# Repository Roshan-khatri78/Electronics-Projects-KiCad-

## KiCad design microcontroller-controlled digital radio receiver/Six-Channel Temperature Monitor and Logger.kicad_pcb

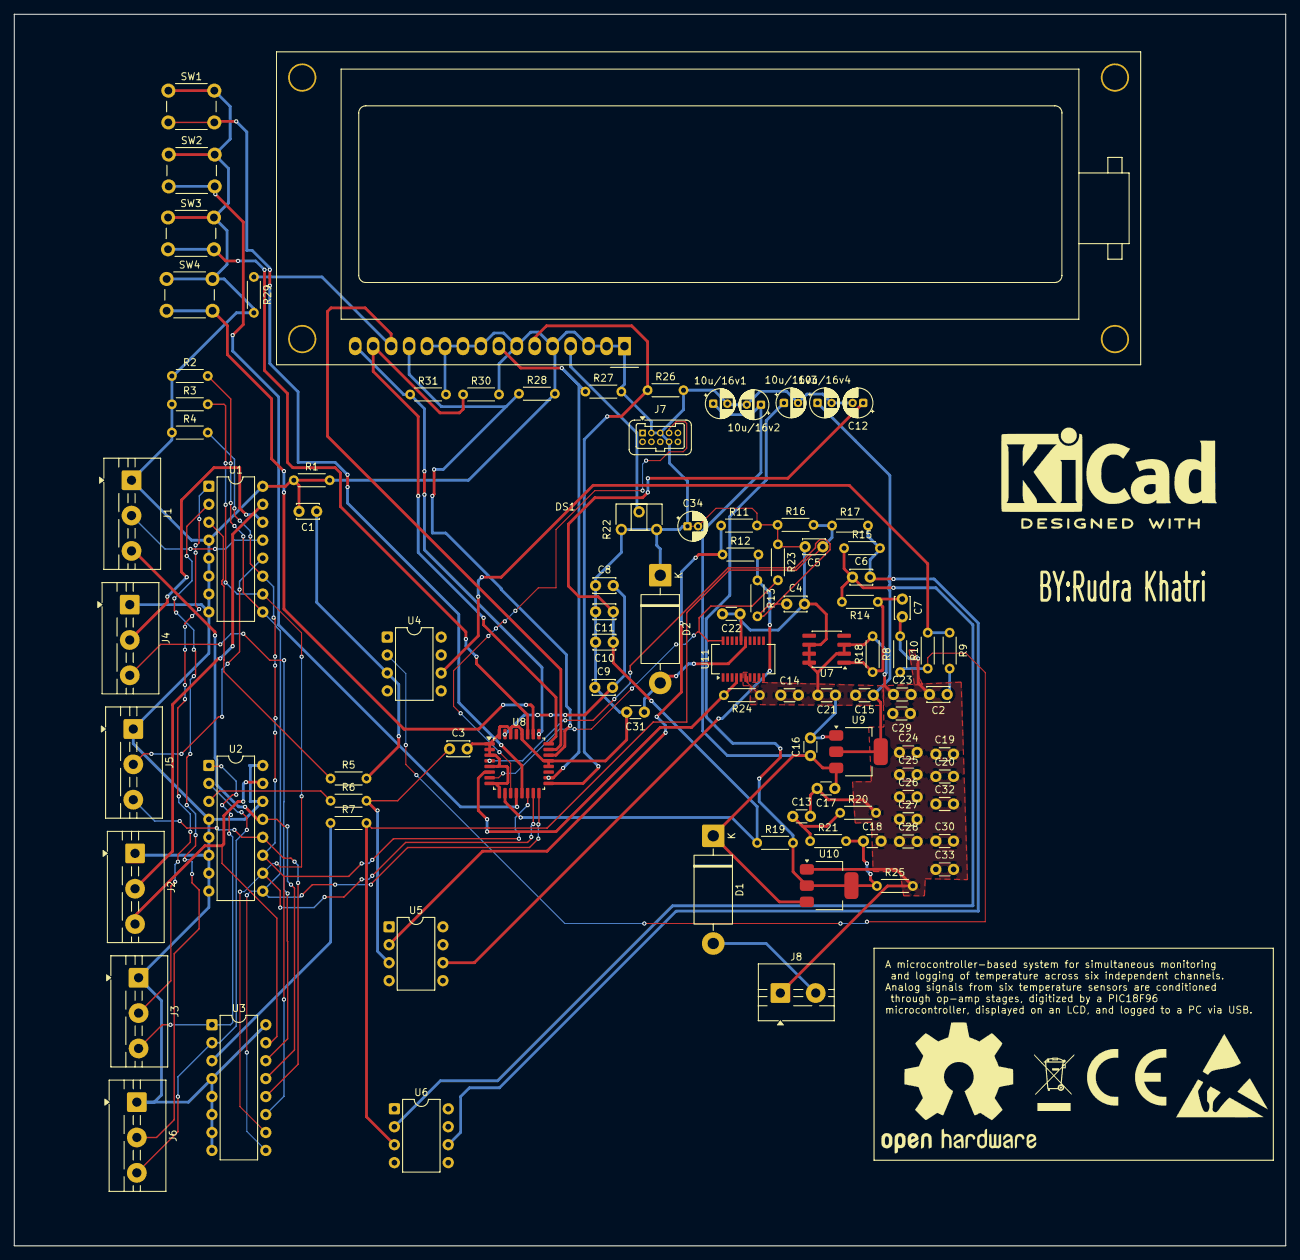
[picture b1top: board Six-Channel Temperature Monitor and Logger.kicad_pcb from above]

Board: 4 copper layers, 179.9 x 174.2 mm, 95 parts (0 on the bottom side), 53 nets.

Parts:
10u/16v1, 10u/16v2, 10u/16v3, 10u/16v4: C_Polarized; CP_Radial_D4.0mm_P2.00mm
C1, C2, C3, C4, C5, C7: C; C_Disc_D3.0mm_W2.0mm_P2.50mm
C6: 1n; C_Disc_D3.0mm_W2.0mm_P2.50mm
C8: 100n; C_Disc_D3.0mm_W2.0mm_P2.50mm
C9, C10, C11: 1; C_Disc_D3.0mm_W2.0mm_P2.50mm
C12: 10v/10u; CP_Radial_D4.0mm_P1.50mm
C13, C14, C15, C16, C17, C18, C31: C; C_Disc_D3.0mm_W1.6mm_P2.50mm
C19, C20, C21, C22, C23, C24, C25, C26, C27, C28, C29, C30, C33: 100n; C_Disc_D3.0mm_W1.6mm_P2.50mm
C32: 1n; C_Disc_D3.0mm_W1.6mm_P2.50mm
C34: 10u/10v; CP_Radial_D4.0mm_P1.50mm
D1, D2: MBR340; D_DO-201AD_P15.24mm_Horizontal
DS1: HY1602E
J1, J2, J3, J4, J5, J6: Screw_Terminal_01x03; TerminalBlock_MaiXu_MX126-5.0-03P_1x03_P5.00mm
J7: Conn_02x05_Odd_Even; Harwin_Gecko-G125-FVX1005L0X_2x05_P1.25mm_Vertical
J8: Screw_Terminal_01x02; TerminalBlock_MaiXu_MX126-5.0-02P_1x02_P5.00mm
R1: 470hm; R_Axial_DIN0204_L3.6mm_D1.6mm_P5.08mm_Horizontal
R2, R3, R4, R14, R15, R16, R17, R23, R24: 10k; R_Axial_DIN0204_L3.6mm_D1.6mm_P5.08mm_Horizontal
R5, R6, R7, R18, R20, R21: 1k; R_Axial_DIN0204_L3.6mm_D1.6mm_P5.08mm_Horizontal
R8, R9, R10, R11, R12, R13, R25, R26, R27, R28, R29, R30, R31: R; R_Axial_DIN0204_L3.6mm_D1.6mm_P5.08mm_Horizontal
R19: 10ohm; R_Axial_DIN0204_L3.6mm_D1.6mm_P5.08mm_Horizontal
R22: Potentiometer; Potentiometer_ACP_CA6-H2,5_Horizontal
SW1, SW2, SW3, SW4: SW_Push; SW_PUSH_6mm_H4.3mm
U1, U2, U3: 4051; DIP-16_W7.62mm
U4, U5, U6: OP07; DIP-8_W7.62mm
U7: TL431D; SOIC-8_3.9x4.9mm_P1.27mm
U8: C8051F350; LQFP-32_7x7mm_P0.8mm
U9, U10: LD1117S12TR_SOT223; SOT-223-3_TabPin2
U11: FT231XS; SSOP-20_3.9x8.7mm_P0.635mm

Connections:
+5V: 10u/16v4.1, C15.1, U9.2 (VO)
+5v: 10u/16v1.2, 10u/16v2.2, 10u/16v3.2, 10u/16v4.2, C1.2, C2.2, C3.2, C4.2, C5.2, C7.2, C8.1, C9.1, C10.2, C11.2, C12.2, C13.2, C14.1, C14.2, C15.2, C16.2, C17.2, C18.2, C19.1, C19.2, C20.1, C20.2, C21.1, C21.2, C22.1, C22.2, C23.1, C23.2, C24.1, C24.2, C25.1, C25.2, C26.1, C26.2, C27.1, C27.2, C28.1, C28.2, C29.1, C29.2, C30.1, C30.2, C31.2, C32.1, C32.2, C33.1, C33.2, C34.1, C34.2, D2.1 (K), DS1.1 (LEDK), DS1.2 (LEDA), DS1.3 (VSS), DS1.5 (Vo), DS1.7 (R/~W), DS1.9 (DB0), DS1.10 (DB1), DS1.11 (DB2), DS1.12 (DB3), J1.1, J2.1, J3.1, J4.1, J5.1, J6.1, J7.2, J7.3, J7.9, J8.1, R1.1, R1.2, R2.1, R3.1, R4.1, R8.2, R11.2, R16.1, R18.2, R20.2, R22.1, R22.3, R23.1, R24.1, R25.2, R26.2, R27.2, R28.2, R29.2, R30.2, R31.2, SW1.1, SW2.1, SW3.1, SW4.1, U1.4 (X7), U1.5 (X5), U1.6 (Inh), U1.7 (VEE), U1.8 (VSS), U1.16 (VDD), U2.4 (X7), U2.5 (X5), U2.6 (Inh), U2.7 (VEE), U2.8 (VSS), U2.14 (X1), U2.16 (VDD), U3.4 (X7), U3.5 (X5), U3.6 (Inh), U3.7 (VEE), U3.8 (VSS), U3.16 (VDD), U7.2 (A), U7.3 (A), U7.6 (A), U7.7 (A), U7.8 (REF), U8.1 (AIN0.2), U8.2 (AIN0.1), U8.3 (GND), U8.5 (AIN0.4), U8.8 (AIN0.7), U8.9 (AGND), U8.20 (DGND), U8.21 (VDD), U8.28 (AIN0.6), U8.30 (AIN0.0), U8.32 (VREF-), U9.1 (GND), U10.1 (GND), U11.6 (GND), U11.16 (GND)
/3v3: 10u/16v3.1, C18.1, R19.2, R21.2, R25.1, U10.2 (VO)
/RXD: R24.2, U8.6 (TX/P0.4), U11.4 (RXD)
/TXD: R23.2, U8.7 (RX/P0.5), U11.20 (TXD)
/a03: C4.1, R13.2, U8.4 (AIN0.3)
/a05: C2.1, R9.2
/ic6: C1.1, R5.2, U4.3 (+)
/ic8: C3.1, R6.2, U5.3 (+)
/ic10: C5.1, R7.2, R16.2, R17.1, U6.3 (+)
/p00: R2.2, U1.9 (C), U2.9 (C), U3.9 (C), U8.16 (P0.0)
/p01: R3.2, U1.10 (B), U2.10 (B), U3.10 (B), U8.15 (P0.1)
/p02: R4.2, U1.11 (A), U2.11 (A), U3.11 (A), U8.14 (P0.2)
/p03: SW1.2, U8.13 (P0.3)
/p06: SW2.2, U8.12 (P0.6)
/p07: SW3.2, U8.27 (P0.7)
/p10: SW4.2, U8.26 (P1.0)
/p11: DS1.16 (DB7), R31.1, U8.25 (P1.1)
/r2: DS1.6 (RS), R26.1, U8.17 (P1.6)
/r3: DS1.8 (E), R27.1, U8.18 (P1.5)
/r4: DS1.13 (DB4), R28.1, U8.22 (P1.4)
/r5: DS1.14 (DB5), R29.1, U8.23 (P1.3)
/r6: DS1.15 (DB6), R30.1, U8.24 (P1.2)
unnamed: C6.2, R15.2, R17.2, U6.6
unnamed: C13.1, R20.1, R21.1
unnamed: D1.2 (A), J8.2
unnamed: 10u/16v1.1, 10u/16v2.1, C16.1, C17.1, D1.1 (K), U9.3 (VI), U10.3 (VI)
unnamed: C31.1, D2.2 (A), U11.15 (VCC)
unnamed: DS1.4 (VDD), R22.2
unnamed: J1.2, U1.13 (X0)
unnamed: J1.3, U2.13 (X0), U3.13 (X0)
unnamed: J2.2, U1.15 (X2)
unnamed: J2.3, U2.15 (X2), U3.15 (X2)
unnamed: J3.2, U1.1 (X4)
unnamed: J3.3, U2.1 (X4), U3.1 (X4)
unnamed: J4.2, U1.14 (X1)
unnamed: J4.3, U3.14 (X1)
unnamed: J5.2, U1.12 (X3)
unnamed: J5.3, U2.12 (X3), U3.12 (X3)
unnamed: J6.2, U1.2 (X6)
unnamed: J6.3, U2.2 (X6), U3.2 (X6)
unnamed: J7.4, U8.11 (P2.0)
unnamed: R9.1, R10.2, U4.6
unnamed: R12.2, R13.1, U5.6
unnamed: R5.1, U1.3 (X)
unnamed: R6.1, U2.3 (X)
unnamed: R7.1, U3.3 (X)
unnamed: R8.1, R10.1, U4.2 (-)
unnamed: R11.1, R12.1, U5.2 (-)
unnamed: C6.1, R14.2, R15.1, U6.2 (-)
unnamed: C7.1, R14.1, R18.1, U7.1 (K)
unnamed: C10.1, C11.1, C12.1, R19.1, U8.10 (AV+)
unnamed: C8.2, C9.2, U8.31 (VREF+)

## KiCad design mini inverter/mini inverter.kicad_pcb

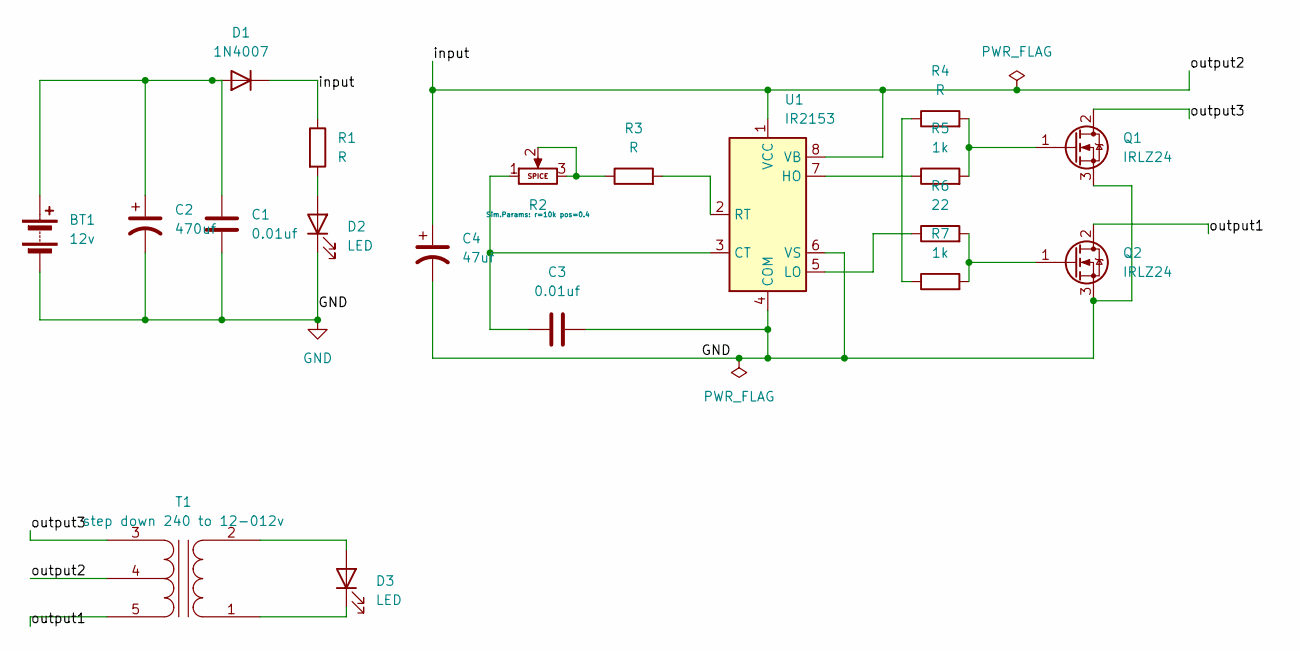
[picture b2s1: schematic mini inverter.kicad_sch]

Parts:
BT1: 12v; TerminalBlock_Phoenix_MKDS-1,5-2_1x02_P5.00mm_Horizontal
C1, C3: 0.01uf; CP_Radial_D5.0mm_P2.50mm
C2: 470uf; CP_Radial_D5.0mm_P2.50mm
C4: 47uf; CP_Radial_D5.0mm_P2.50mm
D1: 1N4007; D_DO-41_SOD81_P10.16mm_Horizontal
D2, D3: LED; LED_D4.0mm
Q1, Q2: IRLZ24; TO-220-3_Vertical
R1, R3, R4: R; R_Axial_DIN0204_L3.6mm_D1.6mm_P5.08mm_Horizontal
R2: Potentiometer; Potentiometer_ACP_CA6-H2,5_Horizontal
R5, R7: 1k; R_Axial_DIN0204_L3.6mm_D1.6mm_P5.08mm_Horizontal
R6: 22; R_Axial_DIN0204_L3.6mm_D1.6mm_P5.08mm_Horizontal
T1: step down 240 to 12-012v; TerminalBlock_MaiXu_MX126-5.0-05P_1x05_P5.00mm
U1: IR2153; DIP-8_W7.62mm

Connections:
/input: C4.1, D1.1 (K), R1.1, T1.4 (SC), U1.1 (VCC), U1.8 (VB)
/output1: Q2.2 (D), T1.5 (SB)
/output3: Q1.2 (D), T1.3 (SA)
GND: BT1.2 (-), C1.2, C2.2, C3.2, C4.2, D2.1 (K), Q1.3 (S), Q2.3 (S), U1.4 (COM), U1.6 (VS)
unnamed: BT1.1 (+), C1.1, C2.1, D1.2 (A)
unnamed: D2.2 (A), R1.2
unnamed: D3.2 (A), T1.2 (AB)
unnamed: D3.1 (K), T1.1 (AA)
unnamed: Q1.1 (G), R4.2, R5.2
unnamed: Q2.1 (G), R6.2, R7.2
unnamed: R2.2, R2.3, R3.1
unnamed: R4.1, R7.1
unnamed: C3.1, R2.1, U1.3 (CT)
unnamed: R5.1, U1.7 (HO)
unnamed: R6.1, U1.5 (LO)
unnamed: R3.2, U1.2 (RT)

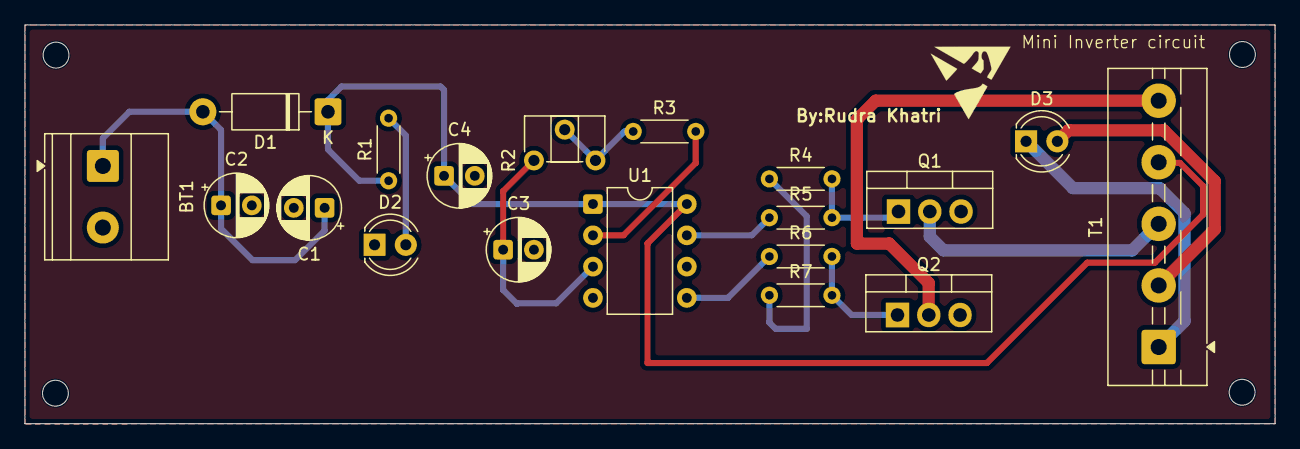
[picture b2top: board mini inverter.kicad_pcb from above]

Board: 2 copper layers, 101.5 x 32.4 mm, 19 parts (0 on the bottom side), 16 nets.

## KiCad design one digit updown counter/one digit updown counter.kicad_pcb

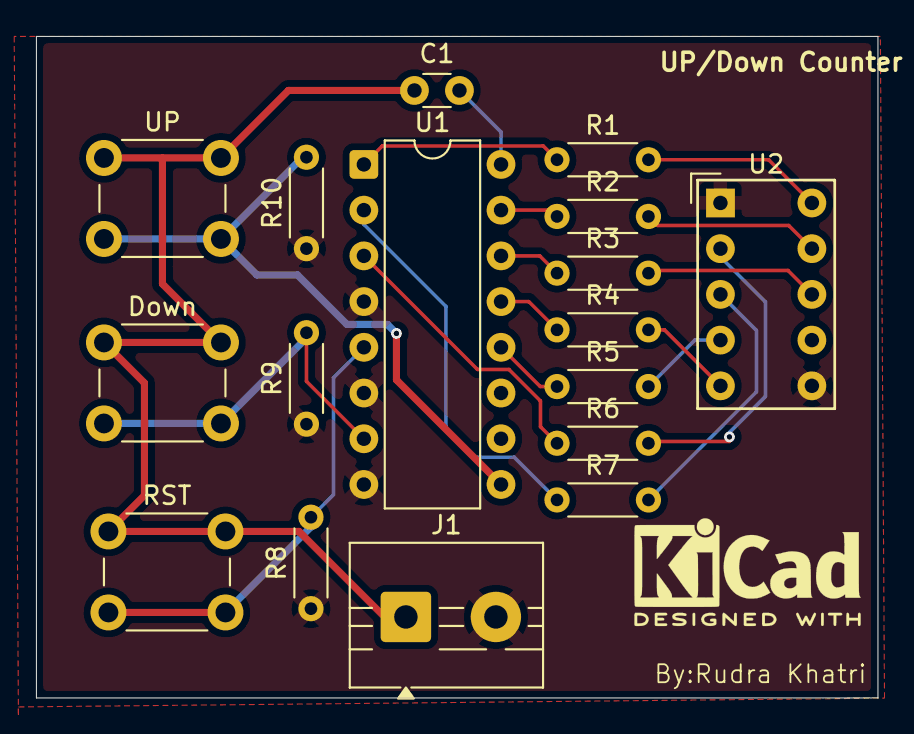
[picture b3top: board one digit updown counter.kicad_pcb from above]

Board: 4 copper layers, 46.8 x 36.8 mm, 17 parts (0 on the bottom side), 20 nets.

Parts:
C1: C; C_Disc_D3.0mm_W1.6mm_P2.50mm
Down: SW_Push; SW_PUSH_6mm_H4.3mm
J1: Screw_Terminal_01x02; TerminalBlock_MaiXu_MX126-5.0-02P_1x02_P5.00mm
R1, R2, R3, R4, R5, R6, R7: 330; R_Axial_DIN0204_L3.6mm_D1.6mm_P5.08mm_Horizontal
R8, R9, R10: 10k; R_Axial_DIN0204_L3.6mm_D1.6mm_P5.08mm_Horizontal
RST: SW_Push; SW_PUSH_6mm_H4.3mm
U1: 40110; DIP-16_W7.62mm
U2: HDSP-7503; HDSP-A151
UP: SW_Push; SW_PUSH_6mm_H4.3mm

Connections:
+5V: C1.1, Down.1, J1.1, RST.1, UP.1
GND: J1.2, R8.1, R9.1, R10.1, U1.4 (~TE), U1.6 (LE), U1.8 (Vss), U2.1 (CC), U2.6 (CC)
unnamed: Down.2, R9.2, U1.7 (CKd)
unnamed: R10.2, U1.9 (CKu), UP.2
unnamed: R8.2, RST.2, U1.5 (CLR)
unnamed: R1.1, U1.1 (Qa)
unnamed: R2.1, U1.15 (Qb)
unnamed: R3.1, U1.14 (Qc)
unnamed: R4.1, U1.13 (Qd)
unnamed: R5.1, U1.12 (Qe)
unnamed: R6.1, U1.3 (Qf)
unnamed: R7.1, U1.2 (Qg)
unnamed: C1.2, U1.16 (Vdd)
unnamed: R1.2, U2.10 (A)
unnamed: R2.2, U2.9 (B)
unnamed: R3.2, U2.8 (C)
unnamed: R4.2, U2.5 (D)
unnamed: R5.2, U2.4 (E)
unnamed: R6.2, U2.2 (F)
unnamed: R7.2, U2.3 (G)

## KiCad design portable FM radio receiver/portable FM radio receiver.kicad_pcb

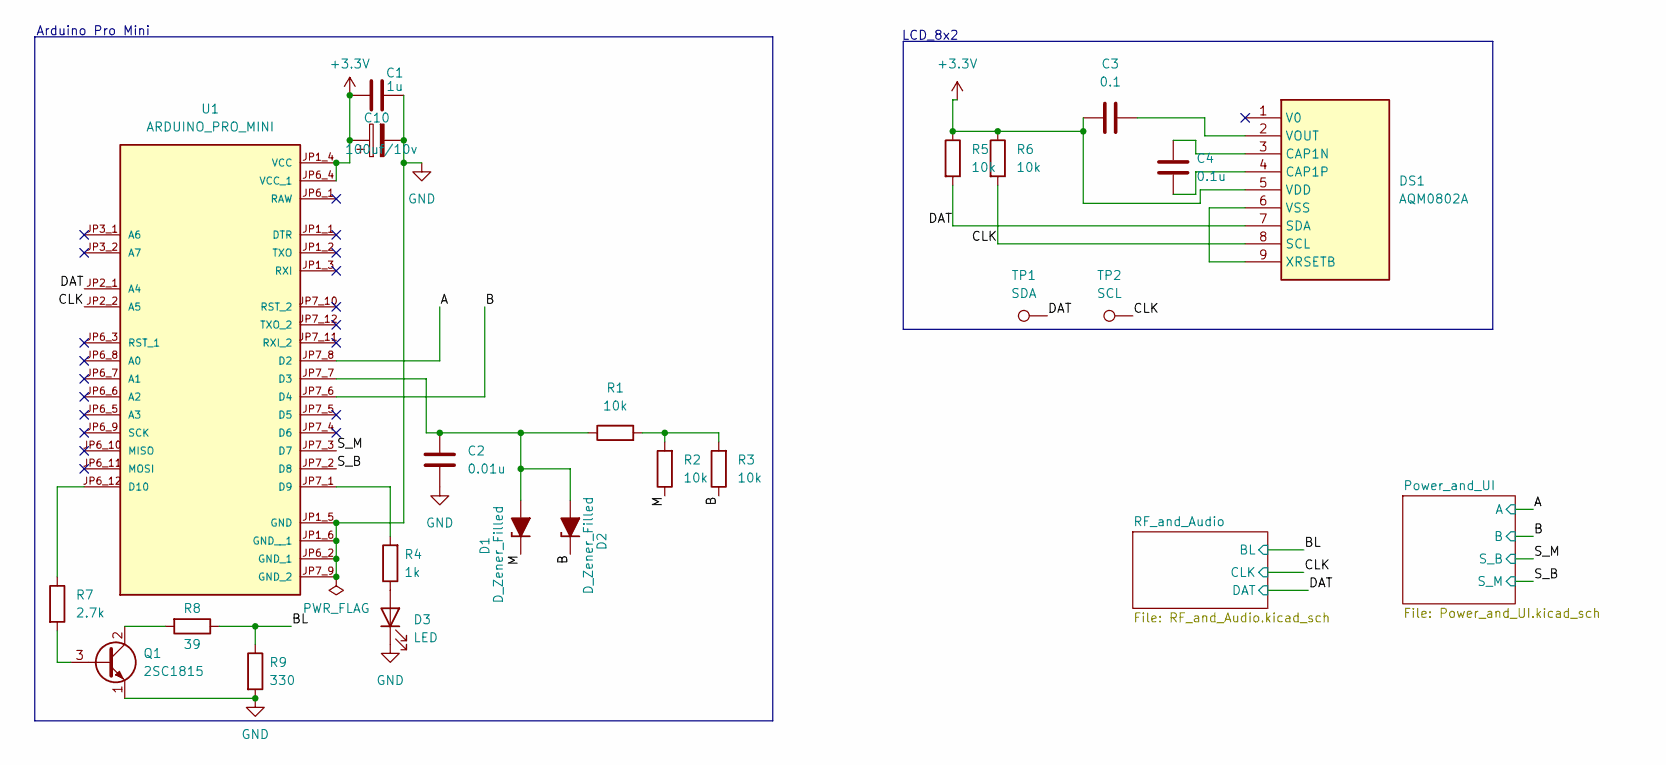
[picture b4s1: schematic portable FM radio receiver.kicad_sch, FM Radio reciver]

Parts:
C1: 1u; C_1825_4564Metric_Pad1.57x6.80mm_HandSolder
C2: 0.01u; C_1825_4564Metric_Pad1.57x6.80mm_HandSolder
C3: 0.1; C_1825_4564Metric_Pad1.57x6.80mm_HandSolder
C4: 0.1u; C_1825_4564Metric_Pad1.57x6.80mm_HandSolder
C10: 100uf/10v; CP_EIA-6032-15_Kemet-U_HandSolder
D1, D2: D_Zener_Filled; D_3220_8050Metric
D3: LED; LED_0805_2012Metric_Pad1.15x1.40mm_HandSolder
DS1: AQM0802A; PinSocket_1x09_P2.54mm_Vertical; Manufacturer_Part_Number AQM0802A
Q1: 2SC1815; TO-220-3_Vertical
R1, R2, R3, R5, R6: 10k; R_0805_2012Metric_Pad1.20x1.40mm_HandSolder
R4: 1k; R_0805_2012Metric_Pad1.20x1.40mm_HandSolder
R7: 2.7k; R_0805_2012Metric_Pad1.20x1.40mm_HandSolder
R8: 39; R_0805_2012Metric_Pad1.20x1.40mm_HandSolder
R9: 330; R_0805_2012Metric_Pad1.20x1.40mm_HandSolder
TP1: SDA; TestPoint_Pad_D2.5mm
TP2: SCL; TestPoint_Pad_D2.5mm
U1: ARDUINO_PRO_MINI; MODULE_ARDUINO_PRO_MINI; PARTREV N/A

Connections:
+3.3V: C1.1, C3.2, C10.1, DS1.5 (VDD), R5.1, R6.1, U1.JP1_4 (VCC), U1.JP6_4 (VCC_1); also elsewhere on the board
/A: U1.JP7_8 (D2); also elsewhere on the board
/B: D2.1 (K), R3.1, U1.JP7_6 (D4); also elsewhere on the board
/BL: R8.1, R9.1; also elsewhere on the board
/CLK: DS1.8 (SCL), R6.2, TP2.1, U1.JP2_2 (A5); also elsewhere on the board
/DAT: DS1.7 (SDA), R5.2, TP1.1, U1.JP2_1 (A4); also elsewhere on the board
/M: D1.1 (K), R2.1
/S_B: U1.JP7_2 (D8); also elsewhere on the board
/S_M: U1.JP7_3 (D7); also elsewhere on the board
GND: C1.2, C2.2, C10.2, D3.1 (K), Q1.1 (E), R9.2, U1.JP1_5 (GND), U1.JP1_6 (GND__1), U1.JP6_2 (GND_1), U1.JP7_9 (GND_2); also elsewhere on the board
unnamed: C2.1, D1.2 (A), D2.2 (A), R1.1, U1.JP7_7 (D3)
unnamed: D3.2 (A), R4.1
unnamed 15: C4.1, DS1.3 (CAP1N); also elsewhere on the board
unnamed 16: C4.2, DS1.4 (CAP1P); also elsewhere on the board
unnamed: DS1.6 (VSS), DS1.9 (XRSETB)
unnamed 18: C3.1, DS1.2 (VOUT); also elsewhere on the board
unnamed: Q1.3 (B), R7.2
unnamed: Q1.2 (C), R8.2
unnamed: R1.2, R2.2, R3.2
unnamed: R4.2, U1.JP7_1 (D9)
unnamed: R7.1, U1.JP6_12 (D10)

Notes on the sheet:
LCD_8x2
Arduino Pro Mini

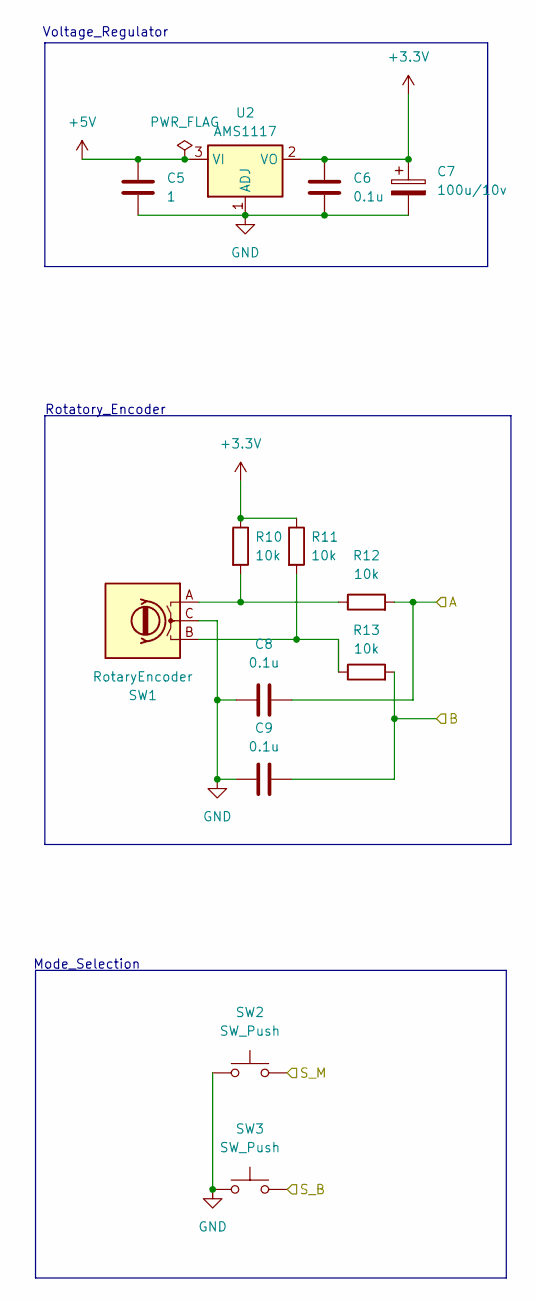
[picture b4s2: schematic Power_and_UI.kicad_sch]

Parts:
C5: 1; C_1825_4564Metric_Pad1.57x6.80mm_HandSolder
C6, C8, C9: 0.1u; C_1825_4564Metric_Pad1.57x6.80mm_HandSolder
C7: 100u/10v; CP_EIA-6032-15_Kemet-U_HandSolder
R10, R11, R12, R13: 10k; R_0805_2012Metric_Pad1.20x1.40mm_HandSolder
SW1: RotaryEncoder; RotaryEncoder_Alps_EC11E_Vertical_H20mm
SW2, SW3: SW_Push; SW_PUSH_6mm_H4.3mm
U2: AMS1117; SOT-223-3_TabPin2

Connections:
+3.3V: C6.1, C7.1, R10.1, R11.1, U2.2 (VO); also elsewhere on the board
+5V: C5.1, U2.3 (VI)
/A: C8.1, R12.2; also elsewhere on the board
/B: C9.1, R13.2; also elsewhere on the board
/S_B: SW2.2; also elsewhere on the board
/S_M: SW3.2; also elsewhere on the board
GND: C5.2, C6.2, C7.2, C8.2, C9.2, SW1.C, SW2.1, SW3.1, U2.1 (ADJ); also elsewhere on the board
unnamed 25: R10.2, R12.1, SW1.A; also elsewhere on the board
unnamed 26: R11.2, R13.1, SW1.B; also elsewhere on the board

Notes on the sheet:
Rotatory_Encoder
Voltage_Regulator
Mode_Selection

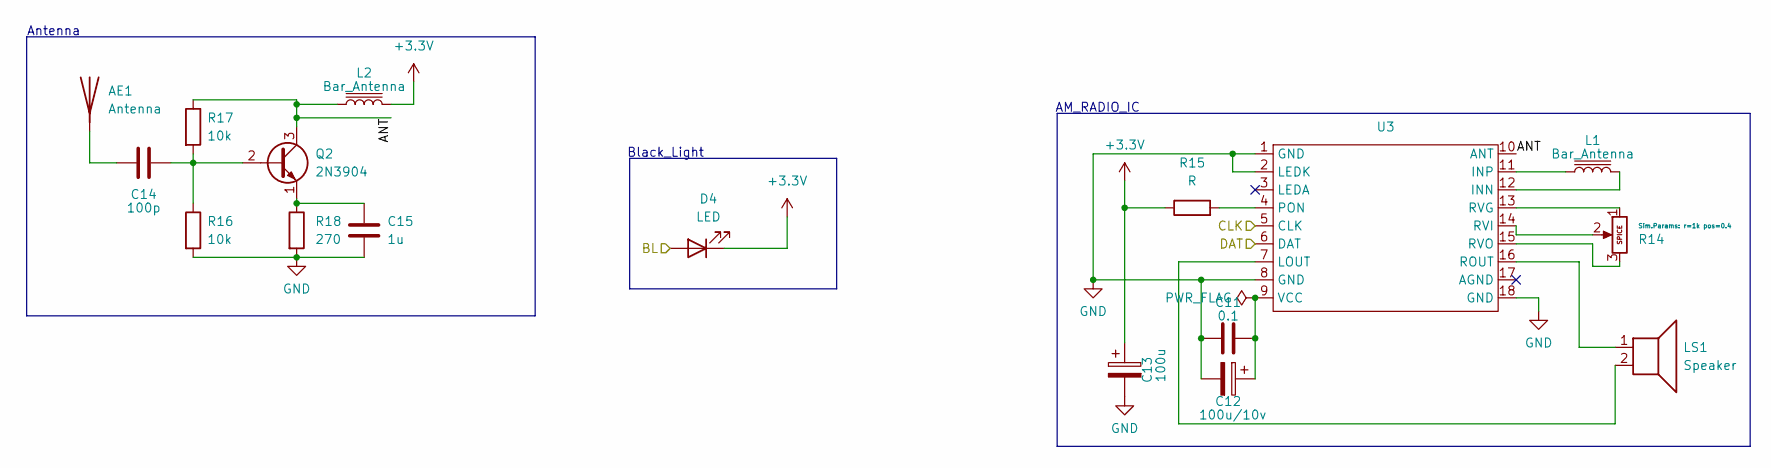
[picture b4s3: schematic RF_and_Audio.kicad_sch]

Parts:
AE1: Antenna; PinHeader_1x01_P2.54mm_Vertical
C11: 0.1; C_1825_4564Metric_Pad1.57x6.80mm_HandSolder
C12: 100u/10v; CP_EIA-6032-15_Kemet-U_HandSolder
C13: 100u; C_1825_4564Metric_Pad1.57x6.80mm_HandSolder
C14: 100p; C_1825_4564Metric_Pad1.57x6.80mm_HandSolder
C15: 1u; C_1825_4564Metric_Pad1.57x6.80mm_HandSolder
D4: LED; LED_0805_2012Metric_Pad1.15x1.40mm_HandSolder
L1, L2: Bar_Antenna; L_Axial_L5.0mm_D3.6mm_P10.00mm_Horizontal_Murata_BL01RN1A2A2
LS1: Speaker; PinHeader_1x02_P2.54mm_Vertical
Q2: 2N3904; TO-220-3_Vertical
R14: Potentiometer; Potentiometer_ACP_CA6-H2,5_Horizontal
R15: R; R_0805_2012Metric_Pad1.20x1.40mm_HandSolder
R16, R17: 10k; R_0805_2012Metric_Pad1.20x1.40mm_HandSolder
R18: 270; R_0805_2012Metric_Pad1.20x1.40mm_HandSolder
U3: SOIC-18W_7.5x11.6mm_P1.27mm

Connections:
+3.3V: C13.1, D4.1 (K), L2.2, R15.1; also elsewhere on the board
/BL: D4.2 (A); also elsewhere on the board
/CLK: U3.5 (CLK); also elsewhere on the board
/DAT: U3.6 (DAT); also elsewhere on the board
/RF_and_Audio/ANT: L2.1, Q2.3 (C), R17.1, U3.10 (ANT)
GND: C11.1, C12.2, C13.2, C15.2, R16.2, R18.2, U3.1 (GND), U3.2 (LEDK), U3.8 (GND), U3.18 (GND); also elsewhere on the board
unnamed: AE1.1 (A_1), C14.1
unnamed: C14.2, Q2.2 (B), R16.1, R17.2
unnamed: C15.1, Q2.1 (E), R18.1
unnamed: L1.2, U3.12 (INN)
unnamed: L1.1, U3.11 (INP)
unnamed: LS1.2, U3.7 (LOUT)
unnamed: R15.2, U3.4 (PON)
unnamed: LS1.1, U3.16 (ROUT)
unnamed: R14.1, U3.13 (RVG)
unnamed: R14.2, U3.14 (RVI)
unnamed: R14.3, U3.15 (RVO)
unnamed: C11.2, C12.1, U3.9 (VCC)

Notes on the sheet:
AM_RADIO_IC
Antenna
Black_Light

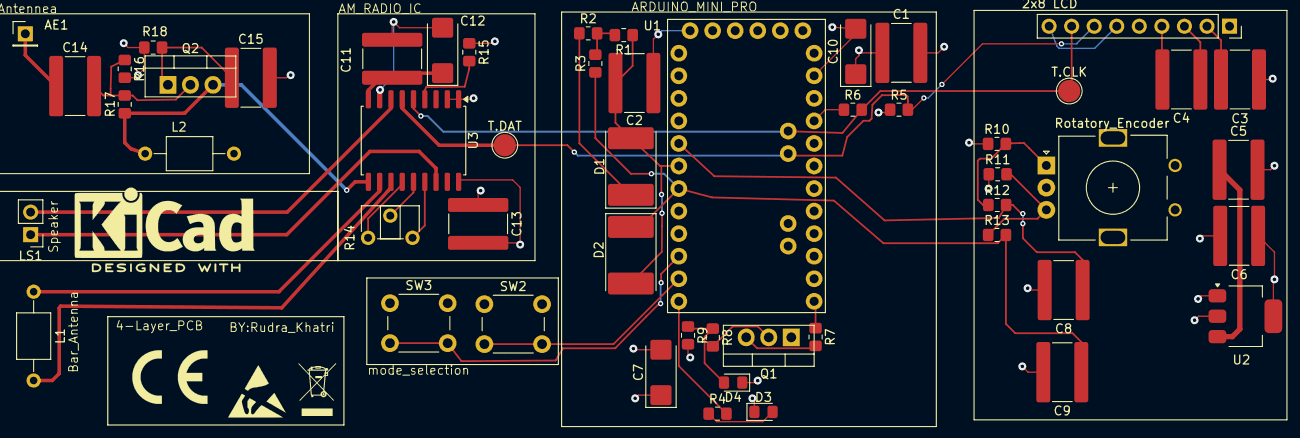
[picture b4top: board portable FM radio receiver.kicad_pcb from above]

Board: 4 copper layers, 52 parts (0 on the bottom side), 37 nets.

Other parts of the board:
2x8 LCD: AQM0802A; PinSocket_1x09_P2.54mm_Vertical
Rotatory_Encoder: RotaryEncoder; RotaryEncoder_Alps_EC11E_Vertical_H20mm
T.CLK: SCL; TestPoint_Pad_D2.5mm
T.DAT: SDA; TestPoint_Pad_D2.5mm

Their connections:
+3.3V: 2x8 LCD.5 (VDD), Rotatory_Encoder.C; also elsewhere on the board
/CLK: 2x8 LCD.8 (SCL), T.CLK.1 (1_1); also elsewhere on the board
/DAT: 2x8 LCD.7 (SDA), T.DAT.1 (1_1); also elsewhere on the board
unnamed 15: 2x8 LCD.3 (CAP1N); also elsewhere on the board
unnamed 16: 2x8 LCD.4 (CAP1P); also elsewhere on the board
unnamed 18: 2x8 LCD.2 (VOUT); also elsewhere on the board
unnamed: 2x8 LCD.6 (VSS), 2x8 LCD.9 (XRSETB)
unnamed 25: Rotatory_Encoder.A; also elsewhere on the board
unnamed 26: Rotatory_Encoder.B; also elsewhere on the board

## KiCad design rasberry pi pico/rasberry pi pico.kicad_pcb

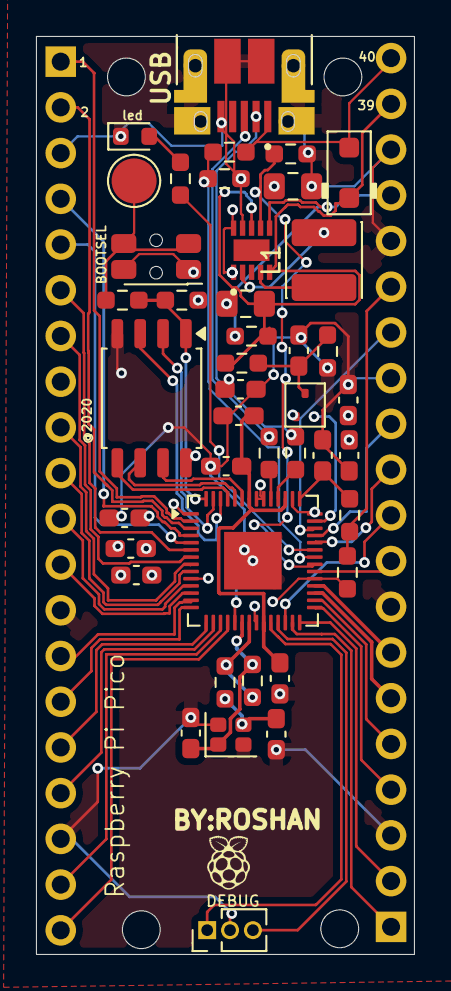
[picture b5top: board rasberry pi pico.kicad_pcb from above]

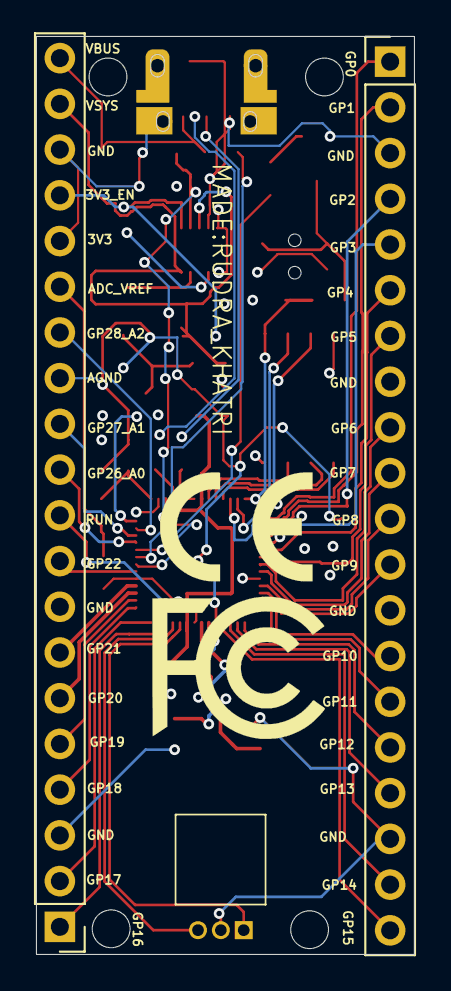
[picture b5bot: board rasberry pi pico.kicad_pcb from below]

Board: 4 copper layers, 21.0 x 51.0 mm, 44 parts (2 on the bottom side), 59 nets.

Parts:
C1, C2, C3, C4, C5, C7, C13: 100n; C_0603_1608Metric_Pad1.08x0.95mm_HandSolder
C6: 100f; C_0603_1608Metric_Pad1.08x0.95mm_HandSolder
C8, C9, C10: 2u2; C_0603_1608Metric_Pad1.08x0.95mm_HandSolder
C11, C12: 47U; C_0805_2012Metric_Pad1.18x1.45mm_HandSolder
C14: 2U; C_0603_1608Metric_Pad1.08x0.95mm_HandSolder
C15: 1N; C_0603_1608Metric_Pad1.08x0.95mm_HandSolder
D1: Green; LED_0603_1608Metric
D2: MBR130SFT; D_SOD-123F
J1: Conn_01x03; PinHeader_1x03_P1.27mm_Vertical
J2, J3: Conn_01x20; PinHeader_1x20_P2.54mm_Vertical
J4: 690-005-298-486; EDAC_690-005-298-486
L1: L; L_Abracon_ASPI-0425
Q1: DMG1012T; SOT-523
R1: 200R; R_0603_1608Metric_Pad0.98x0.95mm_HandSolder
R2: 1R; R_0603_1608Metric_Pad0.98x0.95mm_HandSolder
R3, R4: 27R; R_0603_1608Metric_Pad0.98x0.95mm_HandSolder
R5, R13: -; R_0603_1608Metric_Pad0.98x0.95mm_HandSolder
R6, R12: 1K; R_0603_1608Metric_Pad0.98x0.95mm_HandSolder
R7: 470R; R_0603_1608Metric_Pad0.98x0.95mm_HandSolder
R8, R9, R10, R11, R14: 100K; R_0603_1608Metric_Pad0.98x0.95mm_HandSolder
R15: 200K; R_0603_1608Metric_Pad0.98x0.95mm_HandSolder
SW1: SW_Push; SW_SPST_EVQP7C
TP6: TestPoint_Square; TestPoint_Pad_D2.5mm
U1: RP2040; QFN-56-1EP_7x7mm_P0.4mm_EP3.2x3.2mm
U2: RT6150B-33GQW; SON50P250X250X80-11N
U3: W25Q16JVSS; SOIC-8_5.3x5.3mm_P1.27mm
Y1: Crystal_GND24; Crystal_SMD_2016-4Pin_2.0x1.6mm

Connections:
+1V1: C2.2, C4.2, C8.1, U1.23 (DVDD), U1.45 (VREG_VOUT), U1.50 (DVDD)
+3V3: C1.2, C3.2, C5.2, C7.1, C11.1, C13.1, C14.1, Q1.1 (G), R1.1, R13.2, U1.1 (IOVDD), U1.10 (IOVDD), U1.22 (IOVDD), U1.33 (IOVDD), U1.42 (IOVDD), U1.44 (VREG_VIN), U1.48 (USB_VDD), U1.49 (IOVDD), U2.1 (VOUT), U2.10 (FB), U3.8 (VCC)
/3V3_EN: J3.17, R9.1, U2.6 (EN)
/ADC_AVDD: C6.1, R2.2, U1.43 (ADC_AVDD)
/ADC_VREF: J3.15, R1.2, R2.1
/GPIO0: J2.1, U1.2 (GPIO0)
/GPIO1: J2.2, U1.3 (GPIO1)
/GPIO2: J2.4, U1.4 (GPIO2)
/GPIO3: J2.5, U1.5 (GPIO3)
/GPIO4: J2.6, U1.6 (GPIO4)
/GPIO5: J2.7, U1.7 (GPIO5)
/GPIO6: J2.9, U1.8 (GPIO6)
/GPIO7: J2.10, U1.9 (GPIO7)
/GPIO8: J2.11, U1.11 (GPIO8)
/GPIO9: J2.12, U1.12 (GPIO9)
/GPIO10: J2.14, U1.13 (GPIO10)
/GPIO11: J2.15, U1.14 (GPIO11)
/GPIO12: J2.16, U1.15 (GPIO12)
/GPIO13: J2.17, U1.16 (GPIO13)
/GPIO14: J2.19, U1.17 (GPIO14)
/GPIO15: J2.20, U1.18 (GPIO15)
/GPIO16: J3.1, U1.27 (GPIO16)
/GPIO17: J3.2, U1.28 (GPIO17)
/GPIO18: J3.4, U1.29 (GPIO18)
/GPIO19: J3.5, U1.30 (GPIO19)
/GPIO20: J3.6, U1.31 (GPIO20)
/GPIO21: J3.7, U1.32 (GPIO21)
/GPIO22: J3.9, U1.34 (GPIO22)
/GPIO23: R8.2, U1.35 (GPIO23), U2.7 (PS)
/GPIO24: R10.1, R11.2, U1.36 (GPIO24)
/GPIO25: R7.2, U1.37 (GPIO25)
/GPIO26_ADC0: J3.11, U1.38 (GPIO26/ADC0)
/GPIO27_ADC1: J3.12, U1.39 (GPIO27/ADC1)
/GPIO28_ADC2: J3.14, U1.40 (GPIO28/ADC2)
/GPIO29_ADC3: Q1.2 (S), U1.41 (GPIO29/ADC3)
/QSPI_SCLK: U1.52 (QSPI_SCLK), U3.6 (CLK)
/QSPI_SD0: U1.53 (QSPI_SD0), U3.5 (DI/IO_{0})
/QSPI_SD1: U1.55 (QSPI_SD1), U3.2 (DO/IO_{1})
/QSPI_SD2: U1.54 (QSPI_SD2), U3.3 (~WP/IO_{2})
/QSPI_SD3: U1.51 (QSPI_SD3), U3.7 (~HOLD/~RESET/IO_{3})
/QSPI_SS: R12.1, R13.1, U1.56 (~QSPI_SS), U3.1 (~CS)
/RUN: J3.10, U1.26 (RUN)
/SWCLK: J1.1, U1.24 (SWCLK)
/SWDIO: J1.3, U1.25 (SWDIO)
/USB_DM: J4.2 (D-), R4.1
/USB_DMX: R4.2, U1.46 (USB_DM)
/USB_DP: J4.3 (D+), R3.1
/USB_DPX: R3.2, U1.47 (USB_DP)
/VBUS: D2.2 (A), J3.20, J4.1 (VBUS), R10.2
/VSYS: C12.2, D2.1 (K), J3.19, R9.2, R15.2, U2.5 (VIN), U2.8 (VINA)
/XIN: C9.1, R5.1, U1.20 (XIN), Y1.1
/XOUT: R5.2, R6.2, U1.21 (XOUT)
/XR: C10.1, R6.1, Y1.3
GND: C1.1, C2.1, C3.1, C4.1, C5.1, C6.2, C7.2, C8.2, C9.2, C10.2, C11.2, C12.1, C13.2, C14.2, C15.2, D1.1 (K), J1.2, J2.3, J2.8, J2.13, J2.18, J3.3, J3.8, J3.13, J3.16, J3.18, J4.5 (GND), J4.SH1 (SHIELD), J4.SH2 (SHIELD__1), J4.SH3 (SHIELD__2), J4.SH4 (SHIELD__3), J4.SH5 (SHIELD__4), J4.SH6 (SHIELD__5), R8.1, R11.1, R14.1, SW1.1, U1.19 (TESTEN), U1.57 (GND), U2.3 (GND), U2.9 (GND__1), U3.4 (GND), Y1.2 (G), Y1.4 (G)
unnamed: D1.2 (A), R7.1
unnamed: C15.1, Q1.3 (D), R14.2, R15.1
unnamed: R12.2, SW1.2, TP6.1 (1_1)
unnamed: L1.1, U2.4 (LX1)
unnamed: L1.2, U2.2 (LX2)

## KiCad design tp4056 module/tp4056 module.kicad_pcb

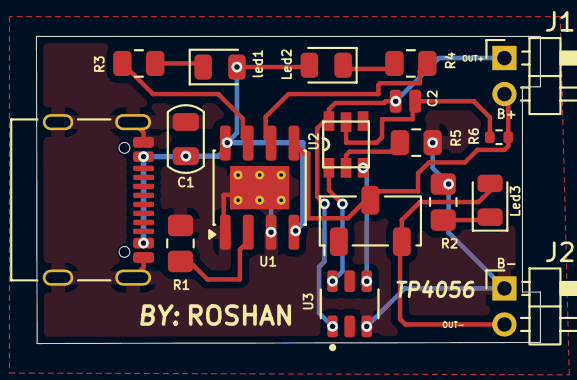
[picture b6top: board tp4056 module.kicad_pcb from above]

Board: 2 copper layers, 28.0 x 17.1 mm, 18 parts (0 on the bottom side), 15 nets.

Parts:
C1: 10uF; C_0805_2012Metric
C2: 1uF; C_0504_1310Metric
IC1: FS312F-G; SOT23-6
J1, J2: Conn_01x02_Pin; PinHeader_1x02_P2.00mm_Horizontal
LED1: LED_2mm_Green; LED_0805_2012Metric
LED2: LED_2mm_Red; LED_0805_2012Metric
LED3: LED_1.8mm_Blue; LED_0805_2012Metric
P1: USB_C_Plug_USB2.0; USB_C_Receptacle_Palconn_UTC16-G
Q1: FS8205; SOT95P280X145-6N
R1, R2: 1K; R_0805_2012Metric
R3: 12K; R_0805_2012Metric_Pad1.20x1.40mm_HandSolder
R4: 2k; R_0805_2012Metric
R5: 100R; R_0402_1005Metric
R6: 4k; R_0805_2012Metric_Pad1.20x1.40mm_HandSolder
SW1: SW_SPDT; Nidec_Copal_CAS-120A
U1: TP4056-42-ESOP8; SOIC-8-1EP_3.9x4.9mm_P1.27mm_EP2.41x3.3mm_ThermalVias

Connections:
/out+: C2.1, IC1.6 (GND), J1.1, Q1.1
/vcc: C1.1, LED1.2 (A), LED2.2 (A), P1.A4 (VBUS), P1.A9 (VBUS), P1.B4 (VBUS), P1.B9 (VBUS), U1.4 (V_{CC}), U1.8 (CE)
GND: C1.2, J2.1, P1.A1 (GND), P1.A12 (GND), P1.B1 (GND), P1.B12 (GND), P1.SH (SHIELD), Q1.3, R3.1, R4.1, R6.1, U1.1 (TEMP), U1.3 (GND), U1.9 (EPAD)
unnamed: IC1.2 (CS), R4.2
unnamed: IC1.3 (OC), Q1.4
unnamed: IC1.1 (OD), Q1.6
unnamed: C2.2, IC1.5 (VCC), R5.2
unnamed: J1.2, R5.1, SW1.2 (B), U1.5 (BAT)
unnamed: J2.2, LED3.2 (A), SW1.3 (C)
unnamed: LED1.1 (K), R1.1
unnamed: LED2.1 (K), R2.1
unnamed: LED3.1 (K), R6.2
unnamed: R3.2, U1.2 (PROG)
unnamed: R1.2, U1.7 (~CHRG)
unnamed: R2.2, U1.6 (~STDBY)
